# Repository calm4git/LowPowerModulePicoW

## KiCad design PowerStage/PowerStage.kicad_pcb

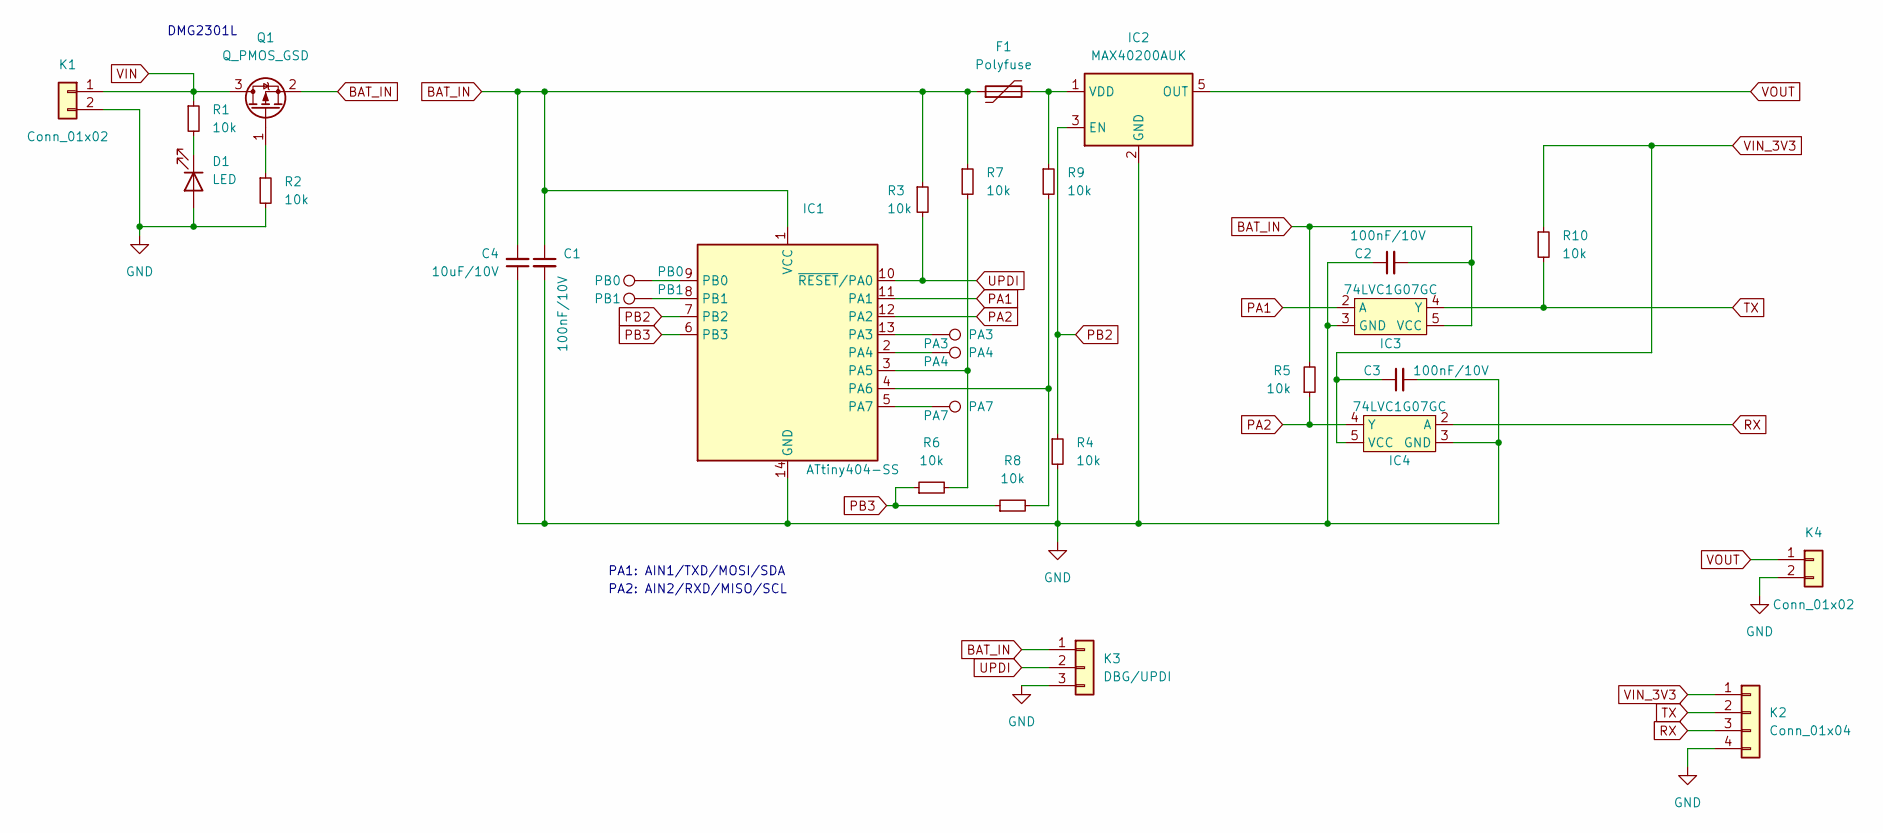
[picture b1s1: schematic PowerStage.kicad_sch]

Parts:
C1, C2, C3: 100nF/10V; C_0805_2012Metric_Pad1.18x1.45mm_HandSolder
C4: 10uF/10V; C_0805_2012Metric_Pad1.18x1.45mm_HandSolder
D1: LED; LED_0805_2012Metric_Pad1.15x1.40mm_HandSolder
F1: Polyfuse; Fuse_1812_4532Metric_Pad1.30x3.40mm_HandSolder
IC1: ATtiny404-SS; SOIC-14_3.9x8.7mm_P1.27mm
IC2: MAX40200AUK; SOT-23-5
IC3, IC4: 74LVC1G07GC; SC-74A
K1, K4: Conn_01x02; PinHeader_1x02_P2.54mm_Vertical
K2: Conn_01x04; PinSocket_1x04_P2.54mm_Vertical
K3: DBG/UPDI; PinHeader_1x03_P2.54mm_Vertical
PA3: PA3; TestPoint_Pad_D1.0mm
PA4: PA4; TestPoint_Pad_D1.0mm
PA7: PA7; TestPoint_Pad_D1.0mm
PB0: PB0; TestPoint_Pad_D1.0mm
PB1: PB1; TestPoint_Pad_D1.0mm
Q1: Q_PMOS_GSD; SOT-23
R1, R2, R3, R4, R5, R6, R7, R8, R9, R10: 10k; R_0805_2012Metric_Pad1.20x1.40mm_HandSolder

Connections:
BAT_IN: C1.1, C2.2, C4.2, F1.1, IC1.1 (VCC), IC3.5 (VCC), K3.1, Q1.2 (S), R3.1, R5.2, R7.1
GND: C1.2, C2.1, C3.2, C4.1, D1.2 (A), IC1.14 (GND), IC2.2 (GND), IC3.3 (GND), IC4.3 (GND), K1.2, K2.4, K3.3, K4.2, R2.2, R4.2
unnamed: D1.1 (K), R1.2
unnamed: F1.2, IC2.1 (VDD), R9.1
unnamed: IC1.2 (PA4), PA4.1
unnamed: IC1.3 (PA5), R6.2, R7.2
unnamed: IC1.4 (PA6), R8.2, R9.2
unnamed: IC1.5 (PA7), PA7.1
unnamed: IC1.8 (PB1), PB1.1
unnamed: IC1.9 (PB0), PB0.1
unnamed: IC1.13 (PA3), PA3.1
unnamed: Q1.1 (G), R2.1
PA1: IC1.11 (PA1), IC3.2 (A)
PA2: IC1.12 (PA2), IC4.4 (Y), R5.1
PB2: IC1.7 (PB2), IC2.3 (EN), R4.1
PB3: IC1.6 (PB3), R6.1, R8.1
RX: IC4.2 (A), K2.3
TX: IC3.4 (Y), K2.2, R10.2
UPDI: IC1.10 (~RESET/PA0), K3.2, R3.2
VIN: K1.1, Q1.3 (D), R1.1
VIN_3V3: C3.1, IC4.5 (VCC), K2.1, R10.1
VOUT: IC2.5 (OUT), K4.1

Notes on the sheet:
PA2: AIN2/RXD/MISO/SCL
DMG2301L
PA1: AIN1/TXD/MOSI/SDA

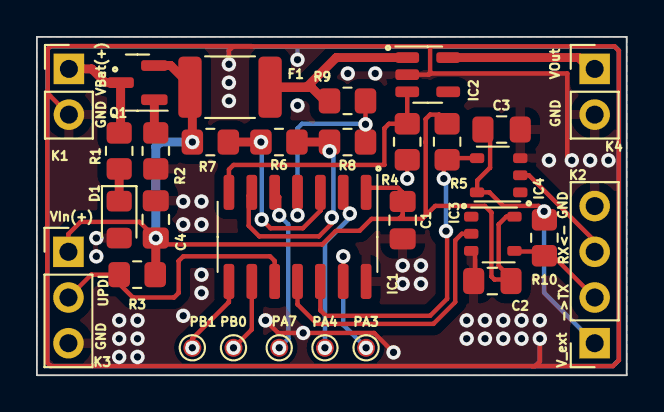
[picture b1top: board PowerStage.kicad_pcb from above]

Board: 2 copper layers, 32.8 x 18.8 mm, 30 parts (0 on the bottom side), 22 nets.

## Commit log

2022-07-10 Initial commit
    Initial Commit, pcb has never been tested and it misses software
2022-07-25 Removed backup files
2022-07-25 Fixes in the schematic
    Some fixes in the schematic
    Not routed
2022-07-25 Schematics changes
    Some modifications in the schematic, need to be routed
2022-08-29 Updated PCB
    PCB and Schamtic has been updated
    Not neeed connections removed
2022-08-29 Files for Rev 2 order
    Designe send to Aisler
